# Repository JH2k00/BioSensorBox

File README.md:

# BioSensorBox
This repository contains the hardware and software for my project in the Advanced Topics in PCB Design lecture at the Technical University of Darmstadt

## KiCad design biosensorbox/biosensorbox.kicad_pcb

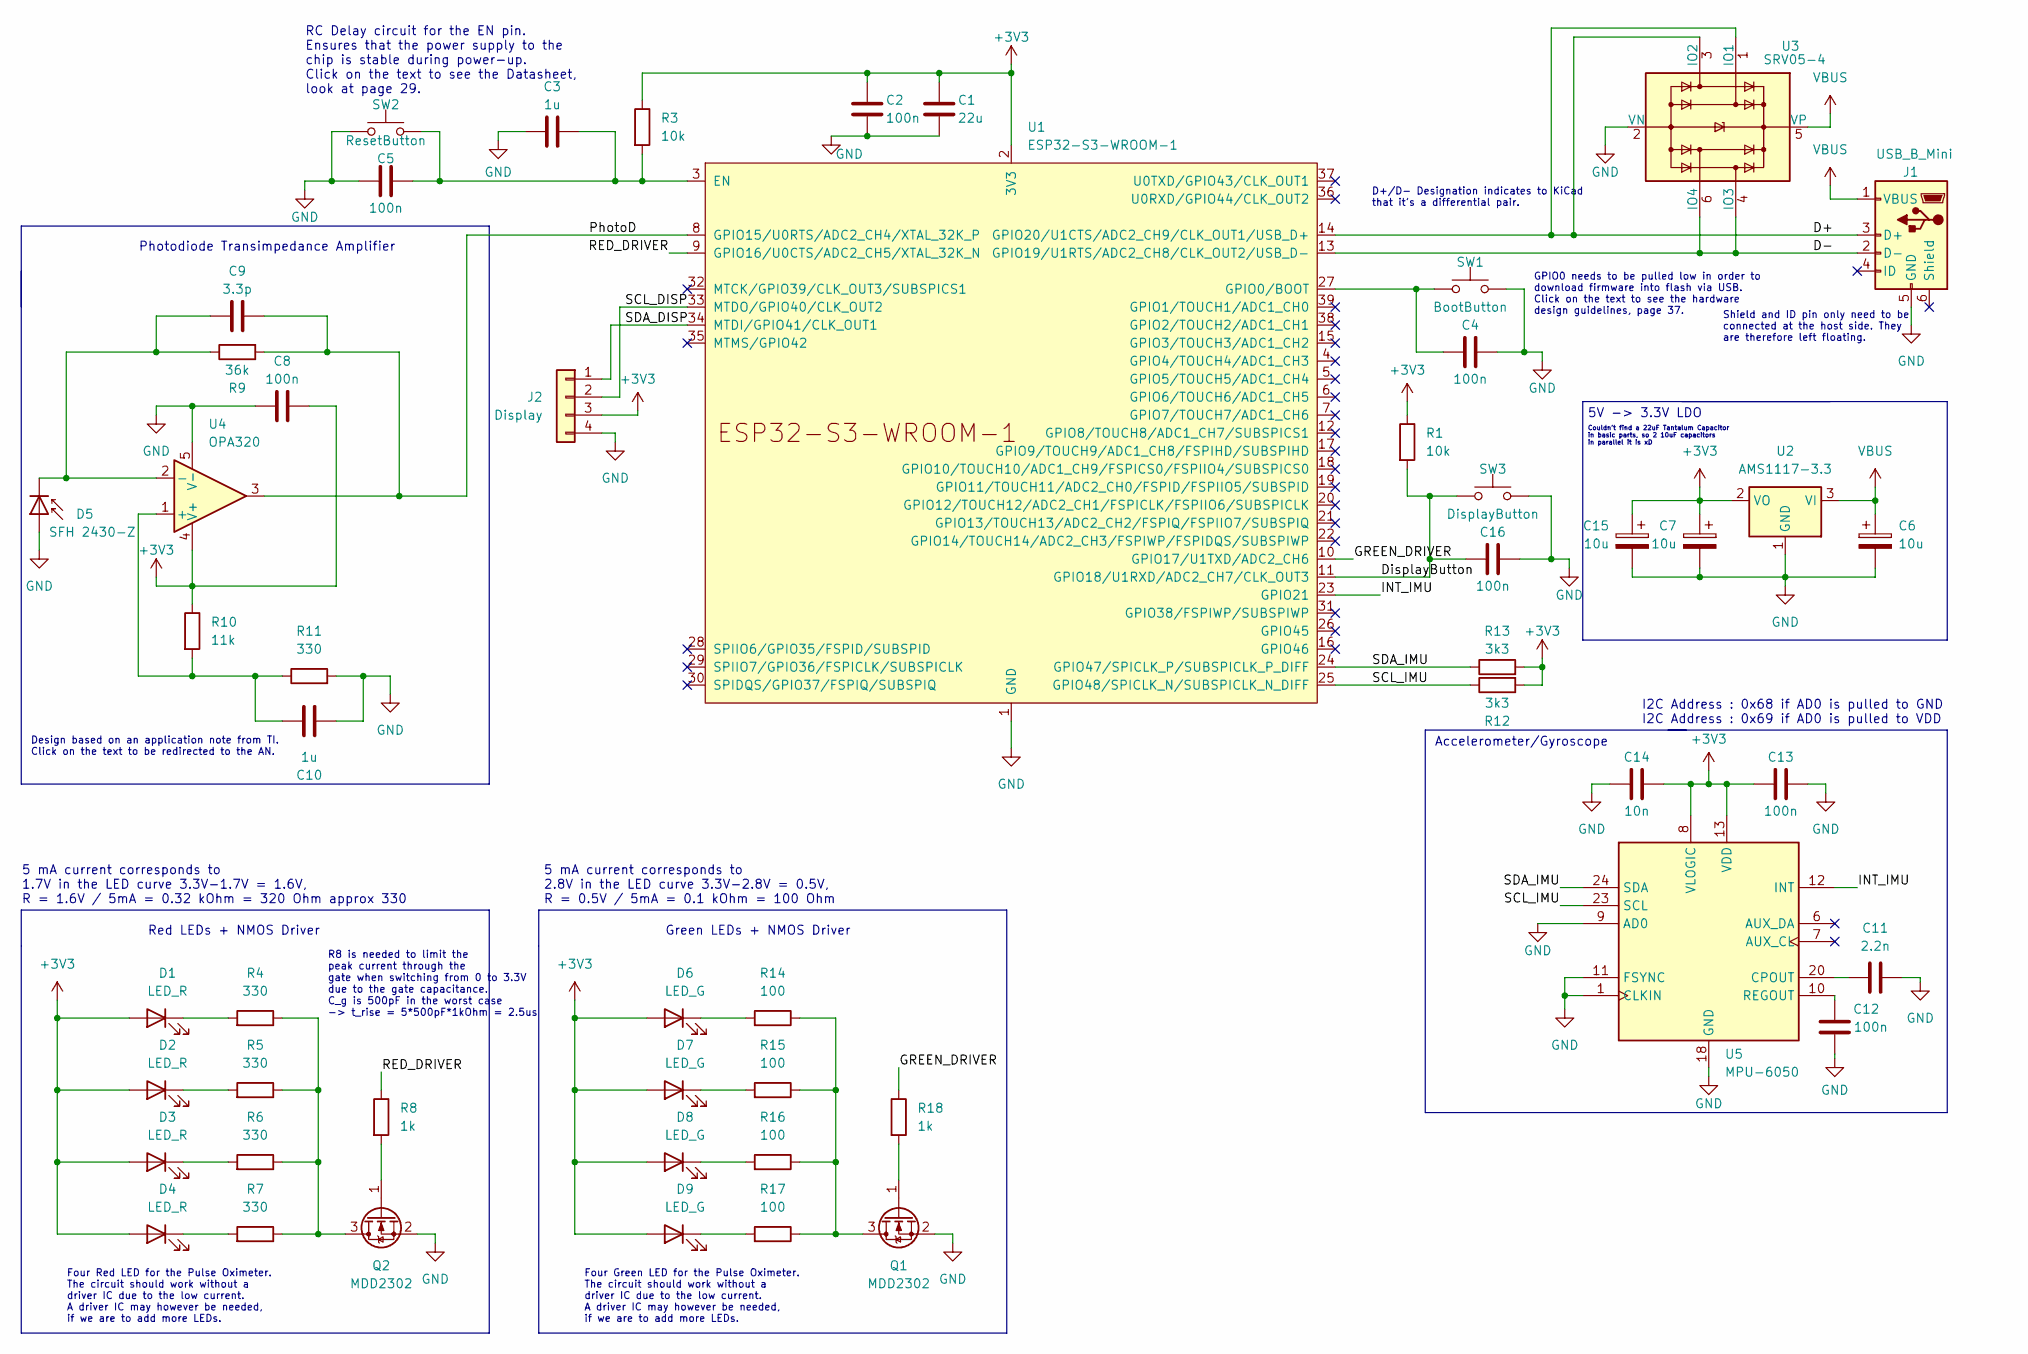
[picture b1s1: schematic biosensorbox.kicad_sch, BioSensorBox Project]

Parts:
C1: 22u; C_1206_3216Metric
C2, C4, C5, C8, C12, C13, C16: 100n; C_0603_1608Metric
C3, C10: 1u; C_0805_2012Metric
C6, C7, C15: 10u; CP_EIA-3216-18_Kemet-A
C9: 3.3p; C_0402_1005Metric
C11: 2.2n; C_0603_1608Metric
C14: 10n; C_0603_1608Metric
D1, D2, D3, D4: LED_R; LED_0603_1608Metric
D5: SFH 2430-Z; Osram_SFH2430
D6, D7, D8, D9: LED_G; LED_0603_1608Metric
J1: USB_B_Mini; USB_Mini-B_Wuerth_65100516121_Horizontal
J2: Display; PinHeader_1x04_P2.54mm_Vertical
Q1, Q2: MDD2302; SOT-23
R1, R3: 10k; R_0603_1608Metric
R4, R5, R6, R7, R11: 330; R_0603_1608Metric
R8, R18: 1k; R_0603_1608Metric
R9: 36k; R_0805_2012Metric
R10: 11k; R_0805_2012Metric
R12, R13: 3k3; R_0603_1608Metric
R14, R15, R16, R17: 100; R_0603_1608Metric
SW1: BootButton; SW_Push_1P1T_XKB_TS-1187A
SW2: ResetButton; SW_Push_1P1T_XKB_TS-1187A
SW3: DisplayButton; SW_Push_1P1T_XKB_TS-1187A
U1: ESP32-S3-WROOM-1
U2: AMS1117-3.3; SOT-223-3_TabPin2
U3: SRV05-4; SOT-23-6
U4: OPA320; SOT-23-5
U5: MPU-6050; InvenSense_QFN-24_4x4mm_P0.5mm

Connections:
+3V3: C1.1, C2.1, C7.1, C8.2, C13.1, C14.1, C15.1, D1.2 (A), D2.2 (A), D3.2 (A), D4.2 (A), D6.2 (A), D7.2 (A), D8.2 (A), D9.2 (A), J2.3, R1.1, R3.1, R10.1, R12.2, R13.2, U1.2 (3V3), U2.2 (VO), U4.4 (V+), U5.8 (VLOGIC), U5.13 (VDD)
/D+: J1.3 (D+), U1.14 (GPIO20/U1CTS/ADC2_CH9/CLK_OUT1/USB_D+), U3.1 (IO1), U3.3 (IO2)
/D-: J1.2 (D-), U1.13 (GPIO19/U1RTS/ADC2_CH8/CLK_OUT2/USB_D-), U3.4 (IO3), U3.6 (IO4)
/DisplayButton: C16.2, R1.2, SW3.2, U1.11 (GPIO18/U1RXD/ADC2_CH7/CLK_OUT3)
/GREEN_DRIVER: R18.1, U1.10 (GPIO17/U1TXD/ADC2_CH6)
/INT_IMU: U1.23 (GPIO21), U5.12 (INT)
/PhotoD: C9.2, R9.2, U1.8 (GPIO15/U0RTS/ADC2_CH4/XTAL_32K_P), U4.3
/RED_DRIVER: R8.1, U1.9 (GPIO16/U0CTS/ADC2_CH5/XTAL_32K_N)
/SCL_DISP: J2.2, U1.33 (MTDO/GPIO40/CLK_OUT2)
/SCL_IMU: R12.1, U1.25 (GPIO48/SPICLK_N/SUBSPICLK_N_DIFF), U5.23 (SCL)
/SDA_DISP: J2.1, U1.34 (MTDI/GPIO41/CLK_OUT1)
/SDA_IMU: R13.1, U1.24 (GPIO47/SPICLK_P/SUBSPICLK_P_DIFF), U5.24 (SDA)
GND: C1.2, C2.2, C3.1, C4.1, C5.1, C6.2, C7.2, C8.1, C10.2, C11.2, C12.2, C13.2, C14.2, C15.2, C16.1, D5.2 (A), J1.5 (GND), J1.6 (Shield), J2.4, Q1.2 (S), Q2.2 (S), R11.2, SW1.1, SW2.1, SW3.1, U1.1 (GND), U1.40 (GND), U1.41 (GND), U2.1 (GND), U3.2 (VN), U4.5 (V-), U5.1 (CLKIN), U5.9 (AD0), U5.11 (FSYNC), U5.18 (GND)
unnamed: D1.1 (K), R4.2
unnamed: D2.1 (K), R5.2
unnamed: D3.1 (K), R6.2
unnamed: D4.1 (K), R7.2
unnamed: C9.1, D5.1 (K), R9.1, U4.2 (-)
unnamed: D6.1 (K), R14.2
unnamed: D7.1 (K), R15.2
unnamed: D8.1 (K), R16.2
unnamed: D9.1 (K), R17.2
unnamed: Q1.3 (D), R14.1, R15.1, R16.1, R17.1
unnamed: Q1.1 (G), R18.2
unnamed: Q2.3 (D), R4.1, R5.1, R6.1, R7.1
unnamed: Q2.1 (G), R8.2
unnamed: C3.2, C5.2, R3.2, SW2.2, U1.3 (EN)
unnamed: C4.2, SW1.2, U1.27 (GPIO0/BOOT)
unnamed: C10.1, R10.2, R11.1, U4.1 (+)
unnamed: C11.1, U5.20 (CPOUT)
unnamed: C12.1, U5.10 (REGOUT)
VBUS: C6.1, J1.1 (VBUS), U2.3 (VI), U3.5 (VP)

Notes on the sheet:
Red LEDs + NMOS Driver
Four Red LED for the Pulse Oximeter. The circuit should work without a driver IC due to the low current. A driver IC may however be needed, if we are to add more LEDs.
Shield and ID pin only need to be connected at the host side. They are therefore left floating.
5 mA current corresponds to 1.7V in the LED curve 3.3V-1.7V = 1.6V, R = 1.6V / 5mA = 0.32 kOhm = 320 Ohm approx 330
D+/D- Designation indicates to KiCad that it's a differential pair.
Four Green LED for the Pulse Oximeter. The circuit should work without a driver IC due to the low current. A driver IC may however be needed, if we are to add more LEDs.
Couldn't find a 22uF Tantalum Capacitor in basic parts, so 2 10uF capacitors in parallel it is xD
5 mA current corresponds to 2.8V in the LED curve 3.3V-2.8V = 0.5V, R = 0.5V / 5mA = 0.1 kOhm = 100 Ohm
Design based on an application note from TI. Click on the text to be redirected to the AN.
I2C Address : 0x68 if AD0 is pulled to GND I2C Address : 0x69 if AD0 is pulled to VDD
GPIO0 needs to be pulled low in order to download firmware into flash via USB. Click on the text to see the hardware design guidelines, page 37.
5V -> 3.3V LDO
Photodiode Transimpedance Amplifier
Green LEDs + NMOS Driver
RC Delay circuit for the EN pin. Ensures that the power supply to the chip is stable during power-up. Click on the text to see the Datasheet, look at page 29.
Accelerometer/Gyroscope
R8 is needed to limit the peak current through the gate when switching from 0 to 3.3V due to the gate capacitance. C_g is 500pF in the worst case -> t_rise = 5*500pF*1kOhm = 2.5us

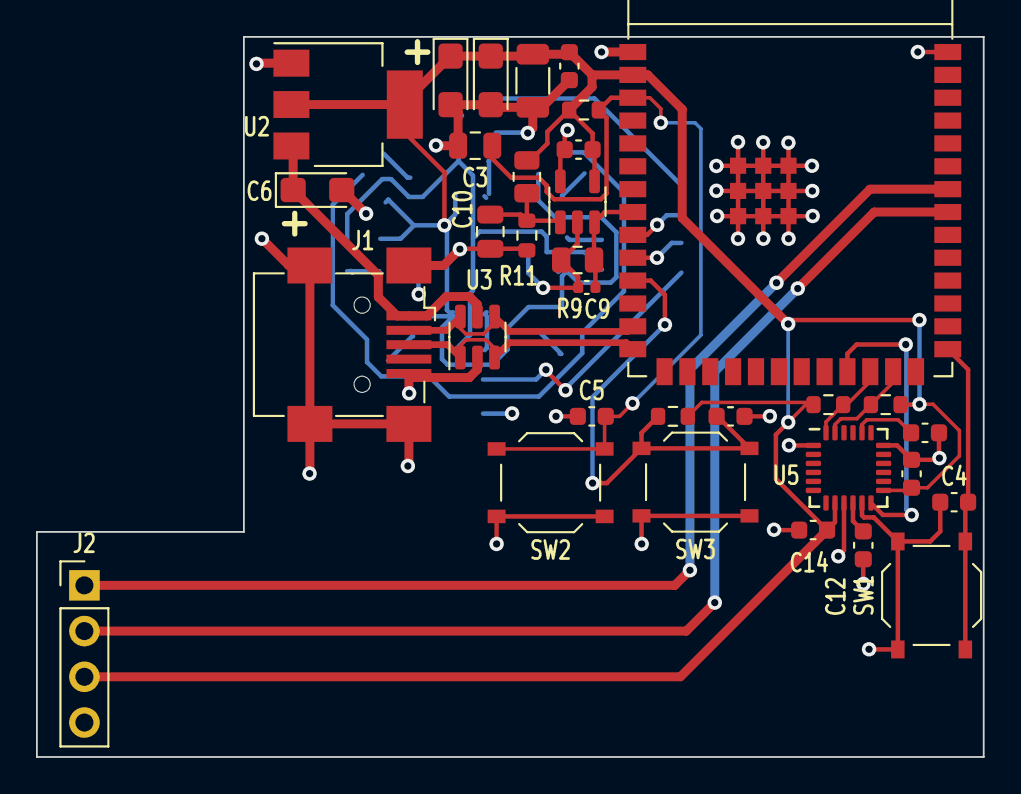
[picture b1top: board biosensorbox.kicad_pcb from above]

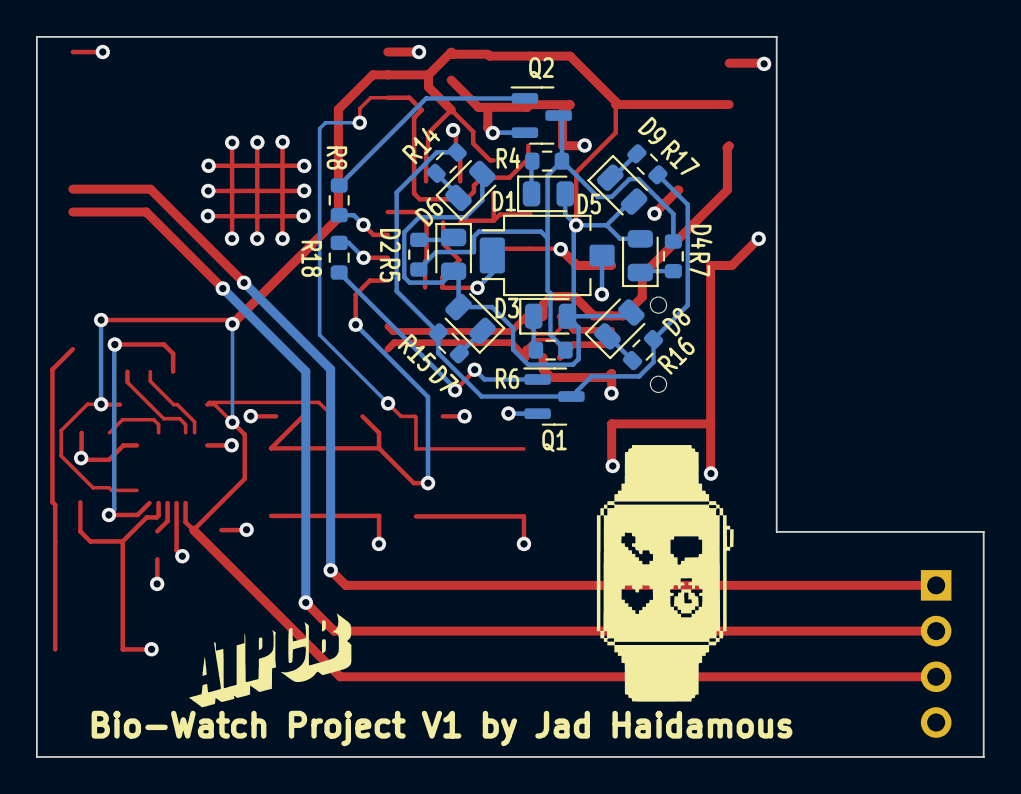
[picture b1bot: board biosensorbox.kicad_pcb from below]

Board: 4 copper layers, 52.6 x 40.0 mm, 54 parts (21 on the bottom side), 32 nets.

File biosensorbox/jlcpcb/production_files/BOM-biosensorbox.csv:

Comment,Designator,Footprint,LCSC
22u,C1,C_1206_3216Metric,C12891
100n,"C12,C13,C16,C2,C4,C5,C8",C_0603_1608Metric,C14663
3.3p,C9,C_0402_1005Metric,C1565
2.2n,C11,C_0603_1608Metric,C1604
11k,R10,R_0805_2012Metric,C17429
1k,"R18,R8",R_0603_1608Metric,C21190
3k3,"R12,R13",R_0603_1608Metric,C22978
330,R11,R_0603_1608Metric,C23138
MPU-6050,U5,InvenSense_QFN-24_4x4mm_P0.5mm,C24112
10k,"R1,R3",R_0603_1608Metric,C25804
1u,"C10,C3",C_0805_2012Metric,C28323
BootButton,"SW1,SW2,SW3",SW_Push_1P1T_XKB_TS-1187A,C318884
USB_B_Mini,J1,USB_Mini-B_Wuerth_65100516121_Horizontal,C428494
36k,R9,R_0805_2012Metric,C4360
10n,C14,C_0603_1608Metric,C57112
AMS1117-3.3,U2,SOT-223-3_TabPin2,C6186
10u,"C15,C6,C7",CP_EIA-3216-18_Kemet-A,C7171
SRV05-4,U3,SOT-23-6,C7420376
OPA320,U4,SOT-23-5,C92494
Display,J2,PinHeader_1x04_P2.54mm_Vertical,
ESP32-S3-WROOM-1,U1,ESP32-S3-WROOM-1,
LED_G,D8,LED_0805_2012Metric,
LED_G,D9,LED_0805_2012Metric,
LED_G,D6,LED_0805_2012Metric,
100,R17,R_0603_1608Metric,
SFH 2430-Z,D5,Osram_SFH2430,
330,R6,R_0603_1608Metric,
LED_R,D2,LED_0805_2012Metric,
330,R7,R_0603_1608Metric,
LED_R,D4,LED_0805_2012Metric,
LED_G,D7,LED_0805_2012Metric,
100,R15,R_0603_1608Metric,
MDD2302,Q2,SOT-23,
100,R16,R_0603_1608Metric,
330,R4,R_0603_1608Metric,
100,R14,R_0603_1608Metric,
330,R5,R_0603_1608Metric,
MDD2302,Q1,SOT-23,
LED_R,D3,LED_0805_2012Metric,
LED_R,D1,LED_0805_2012Metric,

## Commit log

2023-11-26 Almost finished first iteration of the schematic design
2023-11-26 Added pdf version of the current schematic
2023-11-27 Updated DC/DC Converter Capacitor values
2023-12-16 Latest updates to the schematic
2023-12-18 Finished Schematic and started Layout
2023-12-19 Finished layout and generated gerbers ! PCB is done !
2024-02-05 Updated to the newest version of the PCB
